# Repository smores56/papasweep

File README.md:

The Papasweep
=============

The papasweep is a one-handed reversible keyboard designed for typing with the [Taipo layout](https://inkeys.wiki/en/keymaps/taipo). It is based on the [pepesweep](https://github.com/XaycMD/pepesweep), but it is MX, and much wider for accomodating bigger hands.

You can order one by uploading the `papasweep.zip` gerber archive to JLCPCB.

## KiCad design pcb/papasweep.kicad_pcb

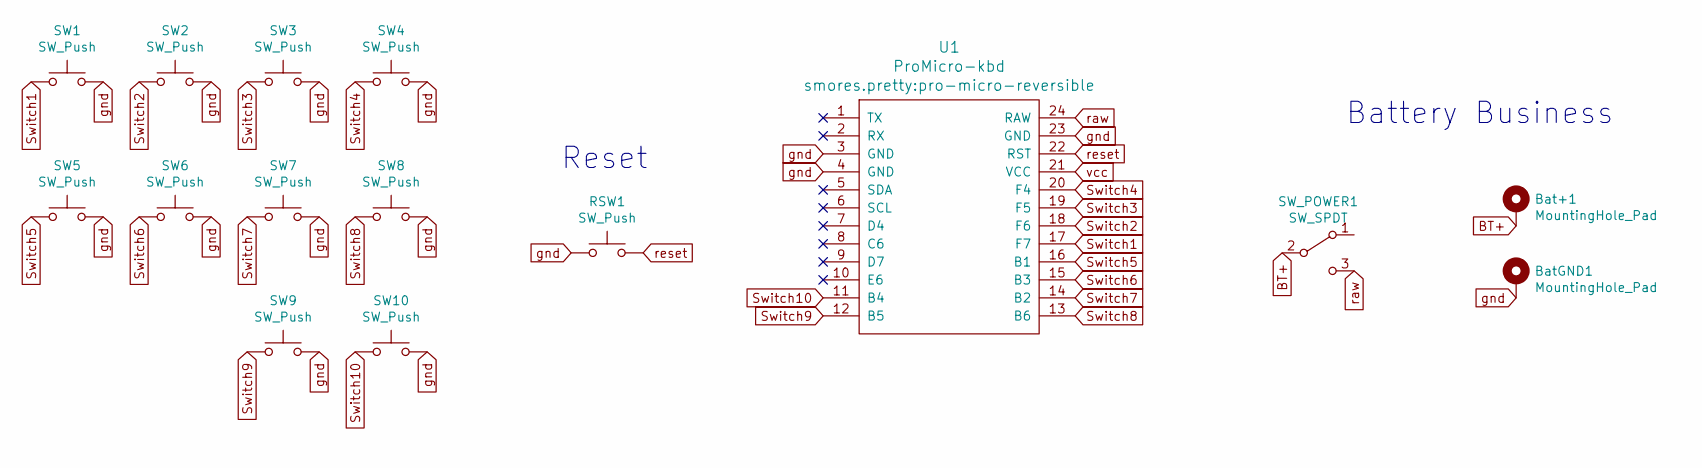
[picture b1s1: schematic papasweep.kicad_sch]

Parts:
Bat+1: MountingHole_Pad; single-pin
BatGND1: MountingHole_Pad; single-pin
RSW1: SW_Push; reset-switch-angled-4pin
SW1, SW2, SW3, SW4, SW5, SW6, SW7, SW8, SW9, SW10: SW_Push; mx-switch-reversible
SW_POWER1: SW_SPDT; power-switch
U1: ProMicro-kbd; pro-micro-reversible

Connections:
BT+: Bat+1.1, SW_POWER1.2 (B)
Switch1: SW1.1, U1.17 (F7)
Switch2: SW2.1, U1.18 (F6)
Switch3: SW3.1, U1.19 (F5)
Switch4: SW4.1, U1.20 (F4)
Switch5: SW5.1, U1.16 (B1)
Switch6: SW6.1, U1.15 (B3)
Switch7: SW7.1, U1.14 (B2)
Switch8: SW8.1, U1.13 (B6)
Switch9: SW9.1, U1.12 (B5)
Switch10: SW10.1, U1.11 (B4)
gnd: BatGND1.1, RSW1.1, SW1.2, SW2.2, SW3.2, SW4.2, SW5.2, SW6.2, SW7.2, SW8.2, SW9.2, SW10.2, U1.3 (GND), U1.4 (GND), U1.23 (GND)
raw: SW_POWER1.3 (C), U1.24 (RAW)
reset: RSW1.2, U1.22 (RST)
vcc: U1.21 (VCC)

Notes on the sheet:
Reset
Battery Business

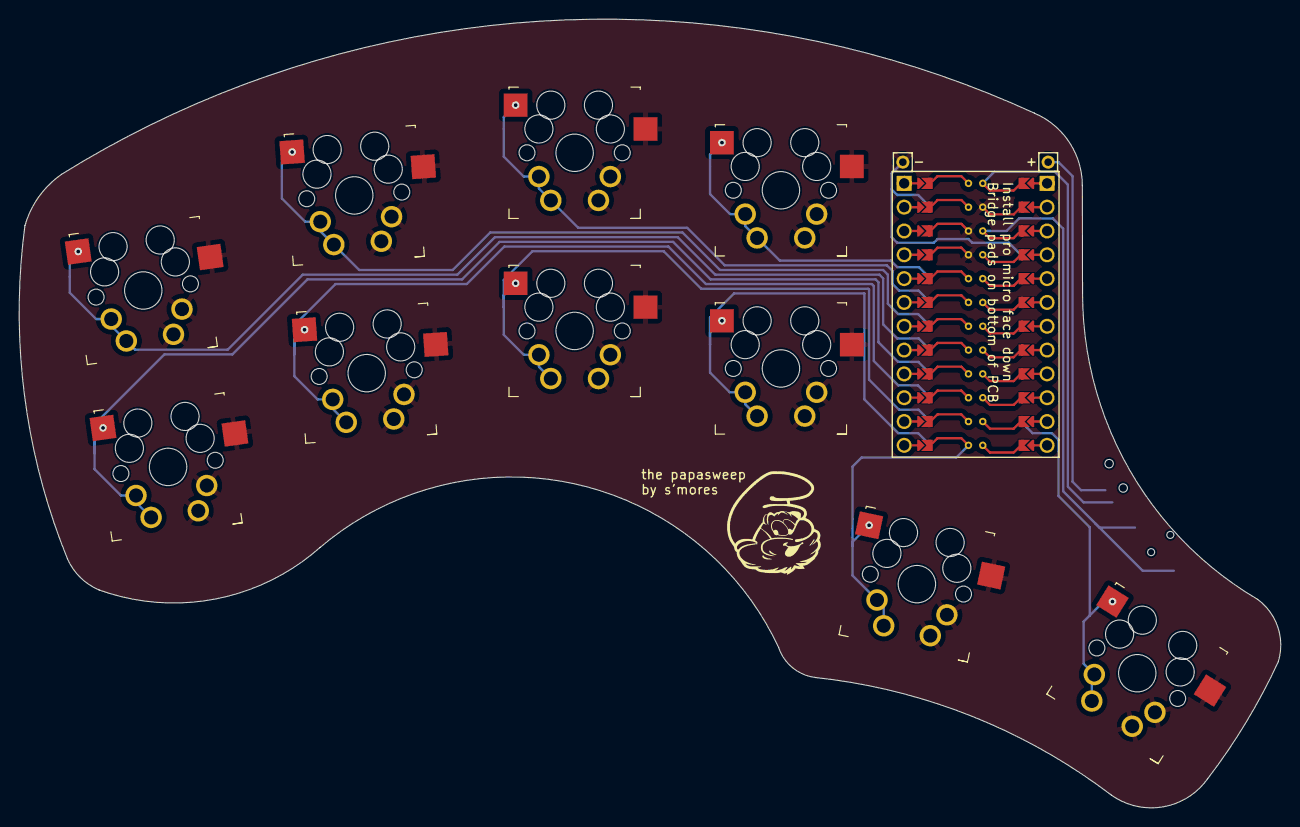
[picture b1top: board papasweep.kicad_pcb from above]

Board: 2 copper layers, 134.5 x 84.1 mm, 15 parts (1 on the bottom side), 14 nets.
